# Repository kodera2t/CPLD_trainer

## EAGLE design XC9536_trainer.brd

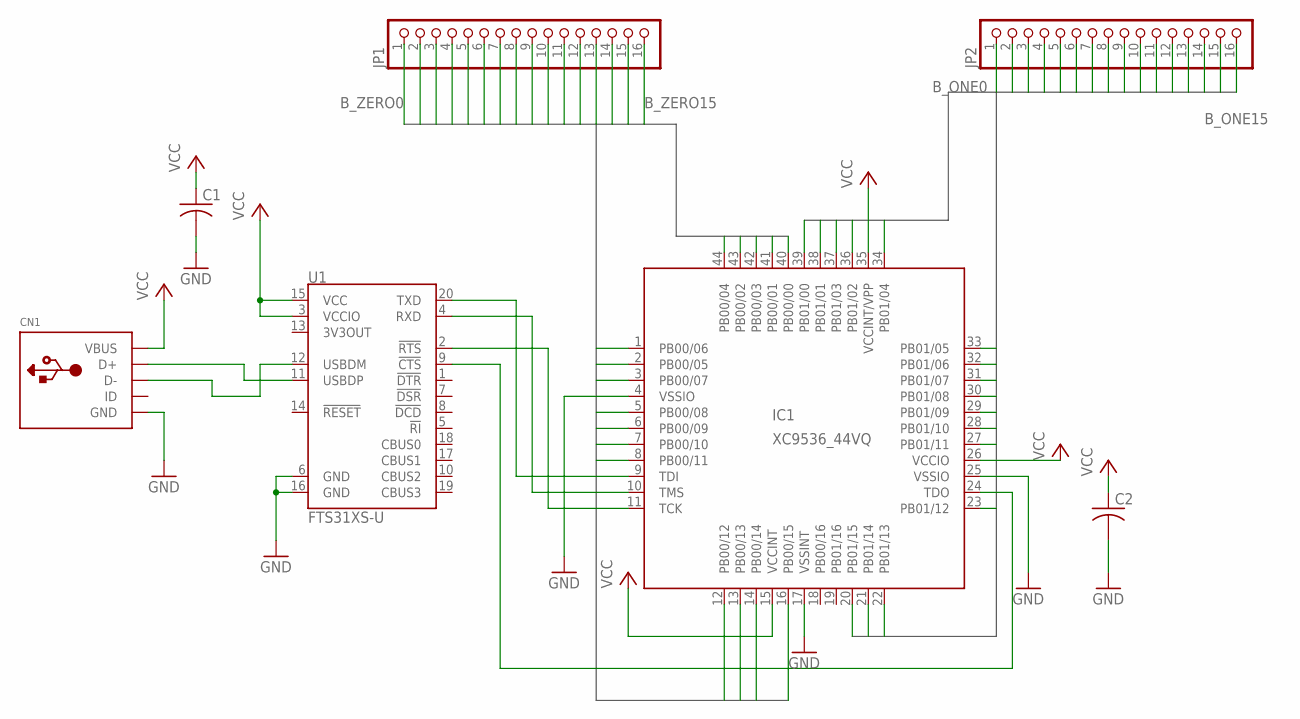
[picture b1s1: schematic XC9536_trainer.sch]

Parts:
C1, C2: C-USC0603K; C0603K
CN1: USBMINIBLARGE; USB-MINIB_LARGER
IC1: XC9536_44VQ; SQFP-S-10X10-44
JP1, JP2: HEADER-1X16ROUND; 1X16_ROUND
U1: FTS31XS-U; SSOP20_L

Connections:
B_ONE0: IC1.39 (PB01/00), JP2.1
B_ONE1: IC1.38 (PB01/01), JP2.2
B_ONE2: IC1.36 (PB01/02), JP2.3
B_ONE3: IC1.37 (PB01/03), JP2.4
B_ONE4: IC1.34 (PB01/04), JP2.5
B_ONE5: IC1.33 (PB01/05), JP2.6
B_ONE6: IC1.32 (PB01/06), JP2.7
B_ONE7: IC1.31 (PB01/07), JP2.8
B_ONE8: IC1.30 (PB01/08), JP2.9
B_ONE9: IC1.29 (PB01/09), JP2.10
B_ONE10: IC1.28 (PB01/10), JP2.11
B_ONE11: IC1.27 (PB01/11), JP2.12
B_ONE12: IC1.23 (PB01/12), JP2.13
B_ONE13: IC1.22 (PB01/13), JP2.14
B_ONE14: IC1.21 (PB01/14), JP2.15
B_ONE15: IC1.20 (PB01/15), JP2.16
B_ZERO0: IC1.40 (PB00/00), JP1.1
B_ZERO1: IC1.41 (PB00/01), JP1.2
B_ZERO2: IC1.43 (PB00/02), JP1.3
B_ZERO3: IC1.42 (PB00/03), JP1.4
B_ZERO4: IC1.44 (PB00/04), JP1.5
B_ZERO5: IC1.2 (PB00/05), JP1.6
B_ZERO6: IC1.1 (PB00/06), JP1.7
B_ZERO7: IC1.3 (PB00/07), JP1.8
B_ZERO8: IC1.5 (PB00/08), JP1.9
B_ZERO9: IC1.6 (PB00/09), JP1.10
B_ZERO10: IC1.7 (PB00/10), JP1.11
B_ZERO11: IC1.8 (PB00/11), JP1.12
B_ZERO12: IC1.12 (PB00/12), JP1.13
B_ZERO13: IC1.13 (PB00/13), JP1.14
B_ZERO14: IC1.14 (PB00/14), JP1.15
B_ZERO15: IC1.16 (PB00/15), JP1.16
GND: C1.2, C2.2, CN1.GND, IC1.4 (VSSIO), IC1.17 (VSSINT), IC1.25 (VSSIO), U1.6 (GND), U1.16 (GND)
unnamed: CN1.D+, U1.11 (USBDP)
unnamed: CN1.D-, U1.12 (USBDM)
unnamed: IC1.9 (TDI), U1.20 (TXD)
unnamed: IC1.10 (TMS), U1.4 (RXD)
unnamed: IC1.11 (TCK), U1.2 (!RTS)
unnamed: IC1.24 (TDO), U1.9 (!CTS)
VCC: C1.1, C2.1, CN1.VBUS, IC1.15 (VCCINT), IC1.26 (VCCIO), IC1.35 (VCCINT/VPP), U1.3 (VCCIO), U1.15 (VCC)

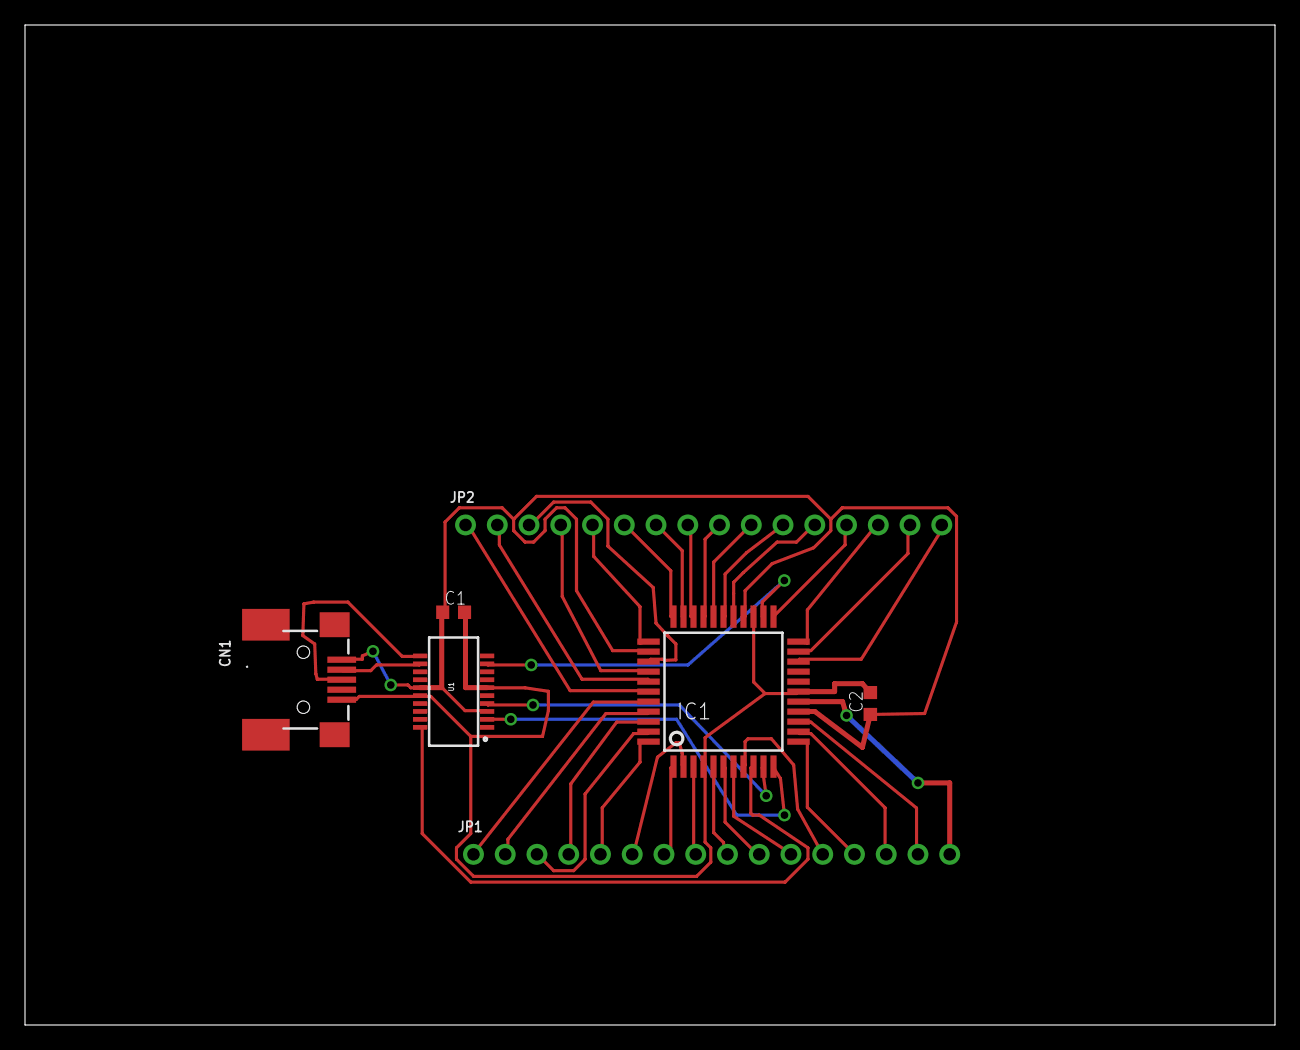
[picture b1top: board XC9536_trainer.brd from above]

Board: 2 copper layers, 100.0 x 80.0 mm, 7 parts (0 on the bottom side), 40 nets.

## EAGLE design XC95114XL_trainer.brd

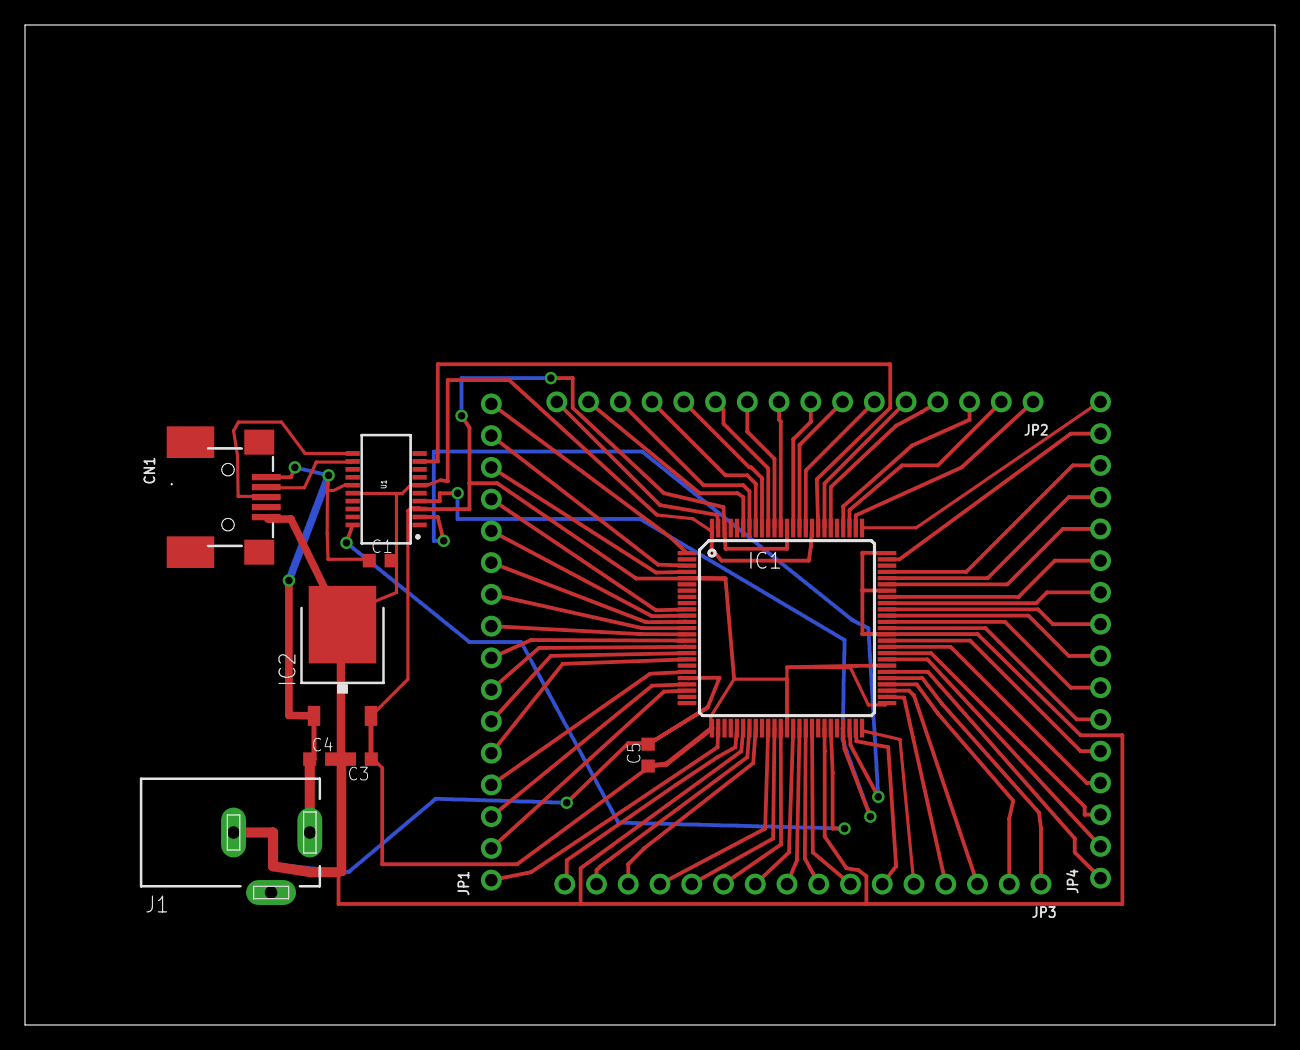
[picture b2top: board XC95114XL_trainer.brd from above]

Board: 2 copper layers, 100.0 x 80.0 mm, 13 parts (0 on the bottom side), 74 nets.

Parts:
C1, C3, C4, C5: C0603K
CN1: USB-MINIB_LARGER
IC1: XC9572XL-TQ100; TQ100
IC2: 7805DT; TO252
J1: DCJ0303
JP1, JP2, JP3, JP4: 1X16_ROUND
U1: FTS31XS-U; SSOP20_L

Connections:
3.3V: C3.1, C5.1, IC1.5, IC1.26, IC1.38, IC1.51, IC1.57, IC1.88, IC1.98, IC2.2, U1.3
+5V: C1.1, C4.1, CN1.VBUS, IC2.1, J1.1, U1.15
GND: C1.2, C3.2, C4.2, C5.2, CN1.GND, IC1.21, IC1.31, IC1.44, IC1.62, IC1.69, IC1.75, IC1.84, IC1.100, IC2.3, J1.3, U1.6, U1.16
unnamed: CN1.D+, U1.11
unnamed: CN1.D-, U1.12
unnamed: IC1.55, JP3.1
unnamed: IC1.54, JP3.2
unnamed: IC1.48, U1.2
unnamed: IC1.53, JP3.3
unnamed: IC1.47, U1.4
unnamed: IC1.45, U1.20
unnamed: IC1.83, U1.9
unnamed: IC1.52, JP3.4
unnamed: IC1.50, JP3.5
unnamed: IC1.49, JP3.6
unnamed: IC1.42, JP3.7
unnamed: IC1.41, JP3.8
unnamed: IC1.40, JP3.9
unnamed: IC1.39, JP3.10
unnamed: IC1.37, JP3.11
unnamed: IC1.36, JP3.12
unnamed: IC1.35, JP3.13
unnamed: IC1.33, JP3.14
unnamed: IC1.32, JP3.15
unnamed: IC1.30, JP3.16
unnamed: IC1.22, JP1.3
unnamed: IC1.23, JP1.2
unnamed: IC1.27, JP1.1
unnamed: IC1.20, JP1.4
unnamed: IC1.18, JP1.5
unnamed: IC1.17, JP1.6
unnamed: IC1.16, JP1.7
unnamed: IC1.15, JP1.8
unnamed: IC1.14, JP1.9
unnamed: IC1.13, JP1.10
unnamed: IC1.12, JP1.11
unnamed: IC1.11, JP1.12
unnamed: IC1.10, JP1.13
unnamed: IC1.1, JP1.16
unnamed: IC1.3, JP1.15
unnamed: IC1.4, JP1.14
unnamed: IC1.56, JP4.1
unnamed: IC1.58, JP4.2
unnamed: IC1.59, JP4.3
unnamed: IC1.60, JP4.4
unnamed: IC1.61, JP4.5
unnamed: IC1.63, JP4.6
unnamed: IC1.64, JP4.7
unnamed: IC1.65, JP4.8
unnamed: IC1.66, JP4.9
unnamed: IC1.67, JP4.10
unnamed: IC1.68, JP4.11
unnamed: IC1.70, JP4.12
unnamed: IC1.71, JP4.13
unnamed: IC1.72, JP4.14
unnamed: IC1.74, JP4.15
unnamed: IC1.76, JP4.16
unnamed: IC1.77, JP2.1
unnamed: IC1.78, JP2.2
unnamed: IC1.79, JP2.3
unnamed: IC1.81, JP2.4
unnamed: IC1.82, JP2.5
unnamed: IC1.85, JP2.6
unnamed: IC1.86, JP2.7
unnamed: IC1.87, JP2.8
unnamed: IC1.89, JP2.9
unnamed: IC1.90, JP2.10
unnamed: IC1.91, JP2.11
unnamed: IC1.92, JP2.12
unnamed: IC1.93, JP2.13
unnamed: IC1.94, JP2.14
unnamed: IC1.95, JP2.15
unnamed: IC1.99, JP2.16
NC: IC1.2, IC1.7, IC1.19, IC1.24, IC1.34, IC1.43, IC1.46, IC1.73, IC1.80

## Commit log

2015-12-12 initial submission
2015-12-21 XC95144XL version
2017-02-01 sample_SVF_file
2017-07-14 Sample svf files for REV2 board

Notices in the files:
parts and their libraries:
OLED_mod: This work is placed in the public domain, and may be freely used for commercial and non-commercial work with the following conditions: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
SparkFun-DigitalIC: Licensing: Creative Commons ShareAlike 4.0 International - https://creativecommons.org/licenses/by-sa/4.0
